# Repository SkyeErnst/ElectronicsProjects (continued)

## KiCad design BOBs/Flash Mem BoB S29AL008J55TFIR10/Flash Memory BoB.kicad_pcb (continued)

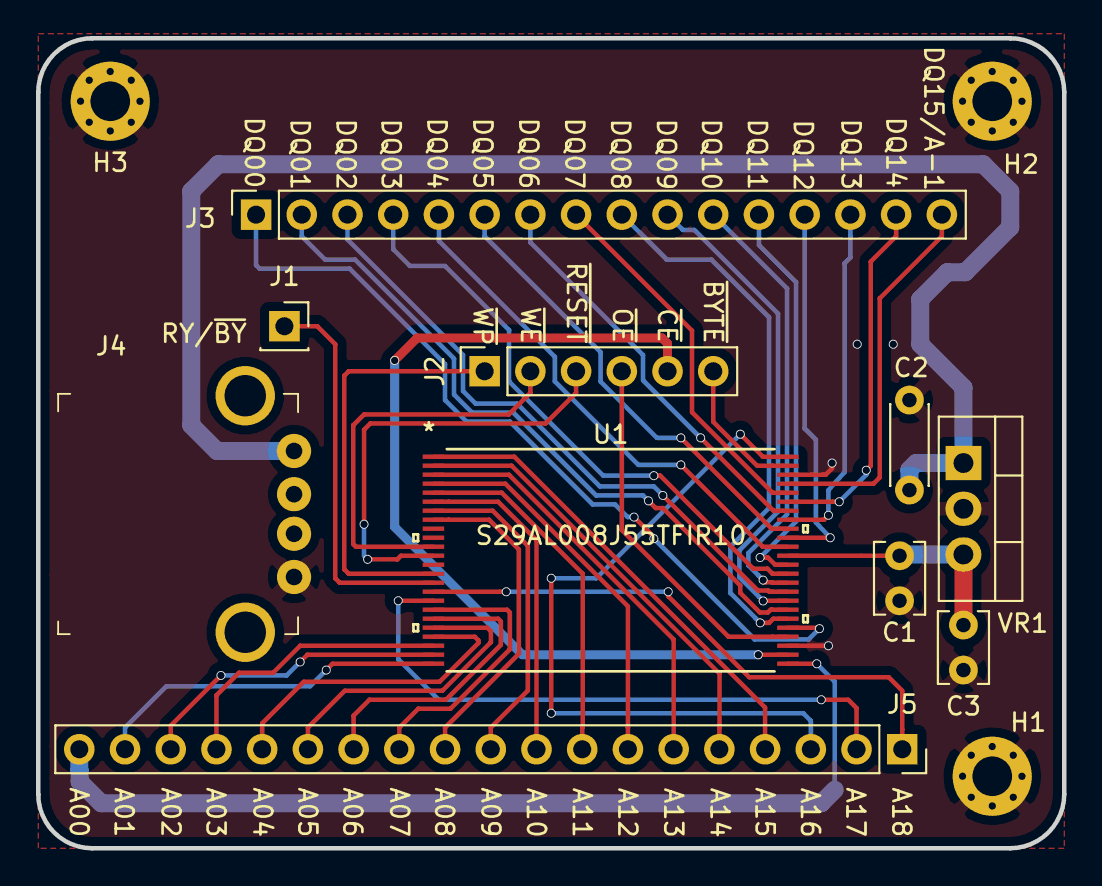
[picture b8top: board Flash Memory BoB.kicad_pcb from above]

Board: 2 copper layers, 57.0 x 45.0 mm, 13 parts (0 on the bottom side), 45 nets.

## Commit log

2021-05-13 Inital commit with gitignore
2021-05-17 try 2
2021-05-30 Added part numbers for mixer OPAMPs
2021-06-01 Added new buffer parts for mixer
2021-06-01 Started work on PCB, annotated schematics
2021-06-02 more pcb work
2021-06-24 First spin of board complete
2021-06-28 Added some footprints from https://github.com/cvra/kicad-lib
    Added specific project for testing mixer and LO on PCB instead of breadboard
2021-06-29 Added components to PCB and set up DRC + board outline
2021-06-29 Freq Count
2021-06-29 Test Board Routed
2021-06-29 Added power regulation, started work on aligning silk screen.
2021-07-01 Added extra filter for testing. Finished silk screen editing.
2021-07-01 Why 12v meme connect to other 12v meme? Grug no know
2021-07-01 Test Board Gerber Output
